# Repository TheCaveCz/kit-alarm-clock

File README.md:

# Alarm clock / Budík

## Česky

Stavebnice digitálních hodin s budíkem ovládaných přes WiFI.

* [Návod na stavbu](doc/manual-cz.md) ([PDF](doc/manual-cz.pdf))
* [Nastavení budíku a aplikace](doc/blynk-cz.md)
* [Nahrání nového firmware](doc/firmware-cz.md)

## English

Coming soon...

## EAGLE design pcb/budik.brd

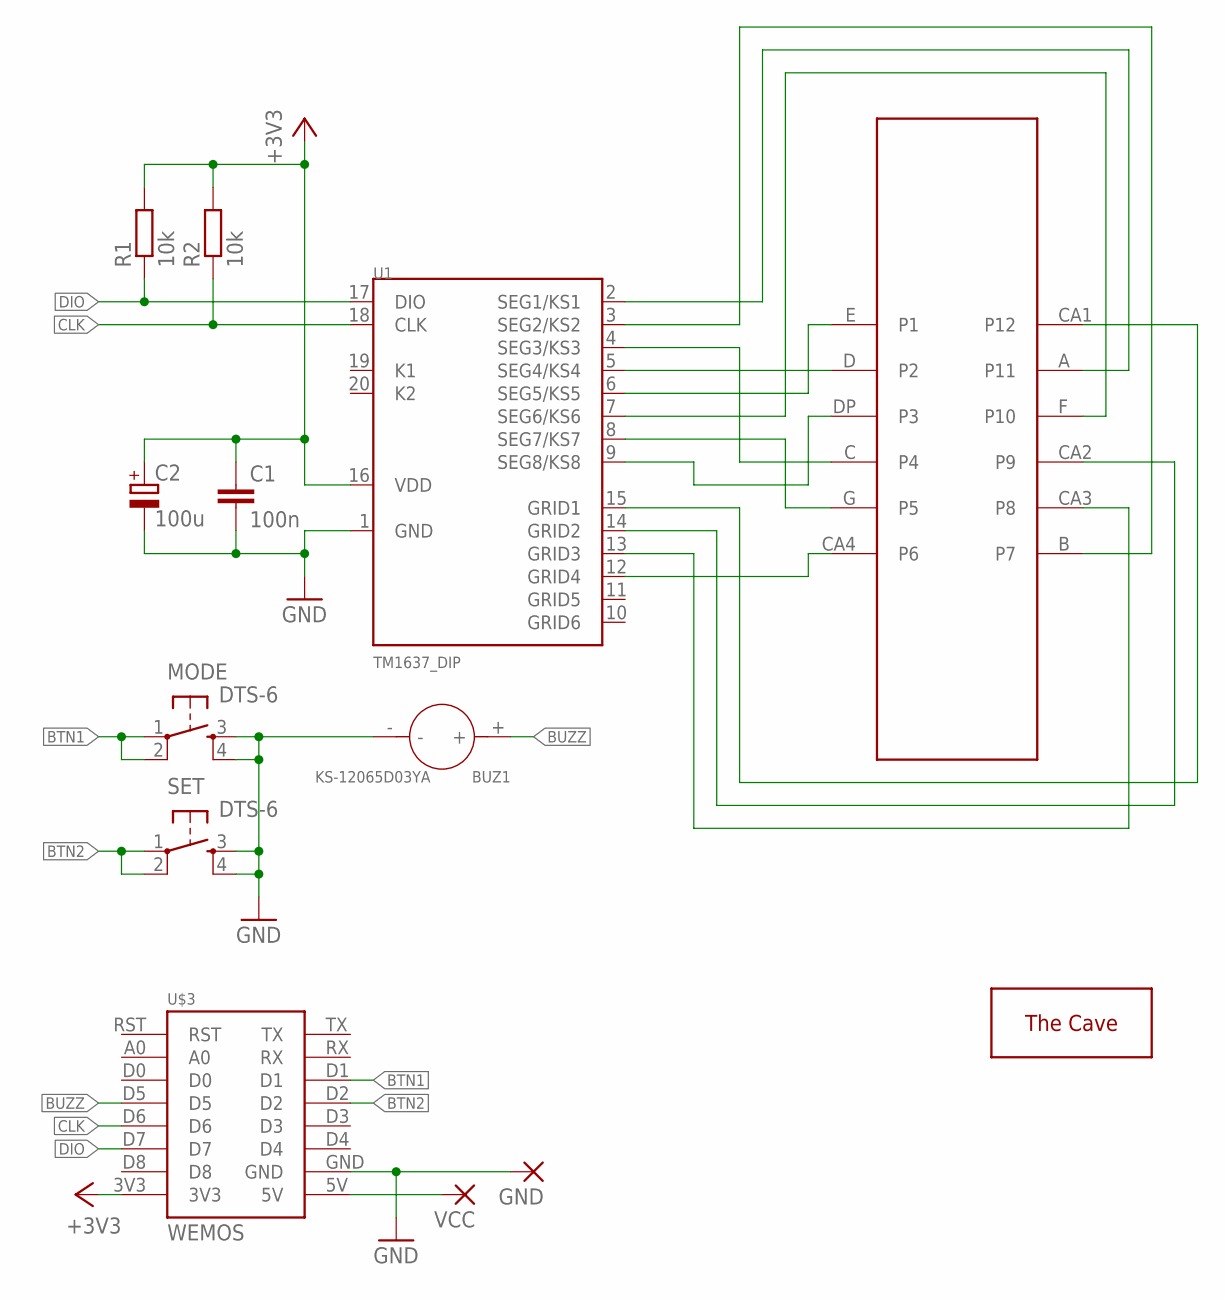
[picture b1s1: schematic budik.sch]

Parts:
BUZ1: KS-12065D03YA; BZ2-7.6-D12.0XH6.5MM
C1: 100n; C025-025X050
C2: 100u; E3,5-8
GND: WIREPADSMD1,27-254; SMD1,27-2,54
MODE: DTS-6
R1, R2: 10k; 0207/7
SET: DTS-6
U1: TM1637_DIP; DIL20
U$1: NFD-5642BX; DISPLAY
U$2: THECAVE_LOGO_NEW_TOP_SMALL; NEW_LOGO_SMALL_TOP
U$3: WEMOS
VCC: WIREPADSMD1,27-254; SMD1,27-2,54

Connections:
+3V3: C1.1, C2.+, R1.2, R2.2, U1.16 (VDD), U$3.3V3
BTN1: MODE.1, MODE.2, U$3.D1
BTN2: SET.1, SET.2, U$3.D2
BUZZ: BUZ1.+, U$3.D5
CLK: R2.1, U1.18 (CLK), U$3.D6
DIO: R1.1, U1.17 (DIO), U$3.D7
GND: BUZ1.-, C1.2, C2.-, GND.1, MODE.3, MODE.4, SET.3, SET.4, U1.1 (GND), U$3.GND
unnamed: U$3.5V, VCC.1
unnamed: U1.2 (SEG1/KS1), U$1.A (P11)
unnamed: U1.3 (SEG2/KS2), U$1.B (P7)
unnamed: U1.4 (SEG3/KS3), U$1.C (P4)
unnamed: U1.5 (SEG4/KS4), U$1.D (P2)
unnamed: U1.6 (SEG5/KS5), U$1.E (P1)
unnamed: U1.7 (SEG6/KS6), U$1.F (P10)
unnamed: U1.8 (SEG7/KS7), U$1.G (P5)
unnamed: U1.9 (SEG8/KS8), U$1.DP (P3)
unnamed: U1.15 (GRID1), U$1.CA1 (P12)
unnamed: U1.14 (GRID2), U$1.CA2 (P9)
unnamed: U1.13 (GRID3), U$1.CA3 (P8)
unnamed: U1.12 (GRID4), U$1.CA4 (P6)

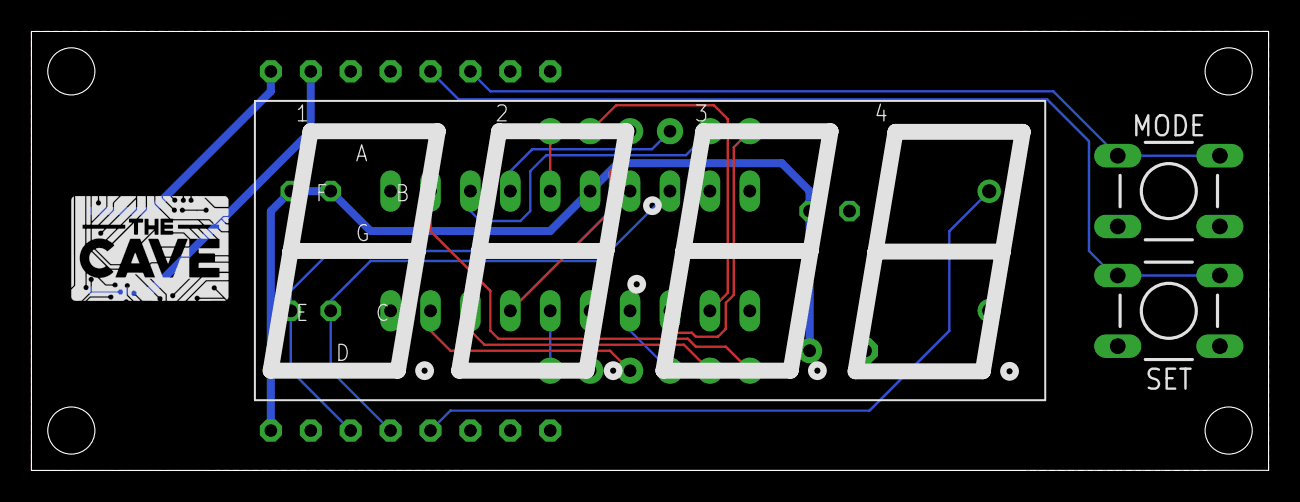
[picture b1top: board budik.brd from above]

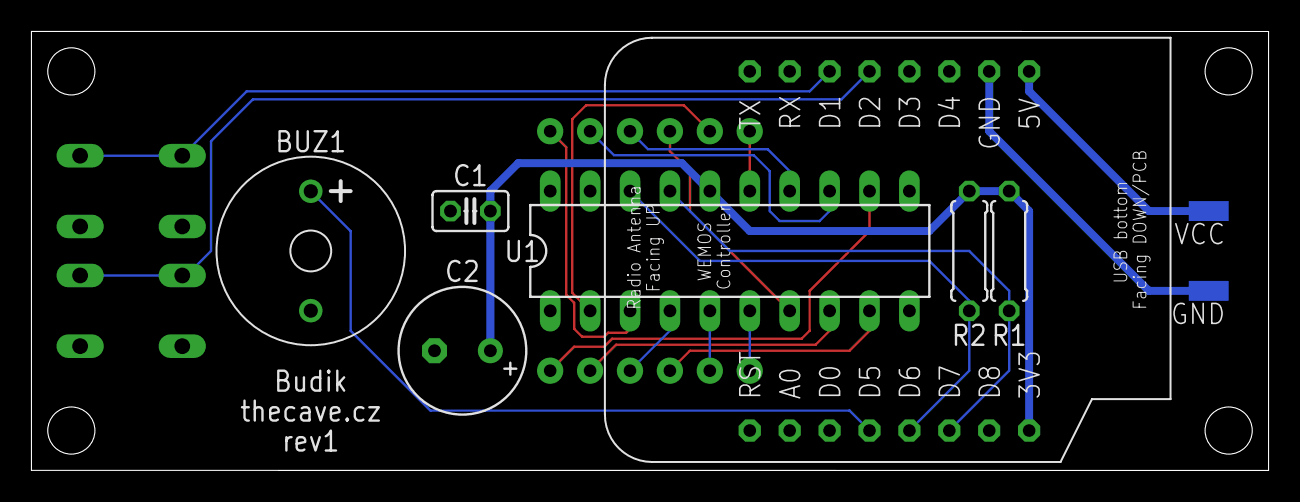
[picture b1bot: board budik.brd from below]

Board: 2 copper layers, 78.7 x 27.9 mm, 13 parts (9 on the bottom side), 20 nets.

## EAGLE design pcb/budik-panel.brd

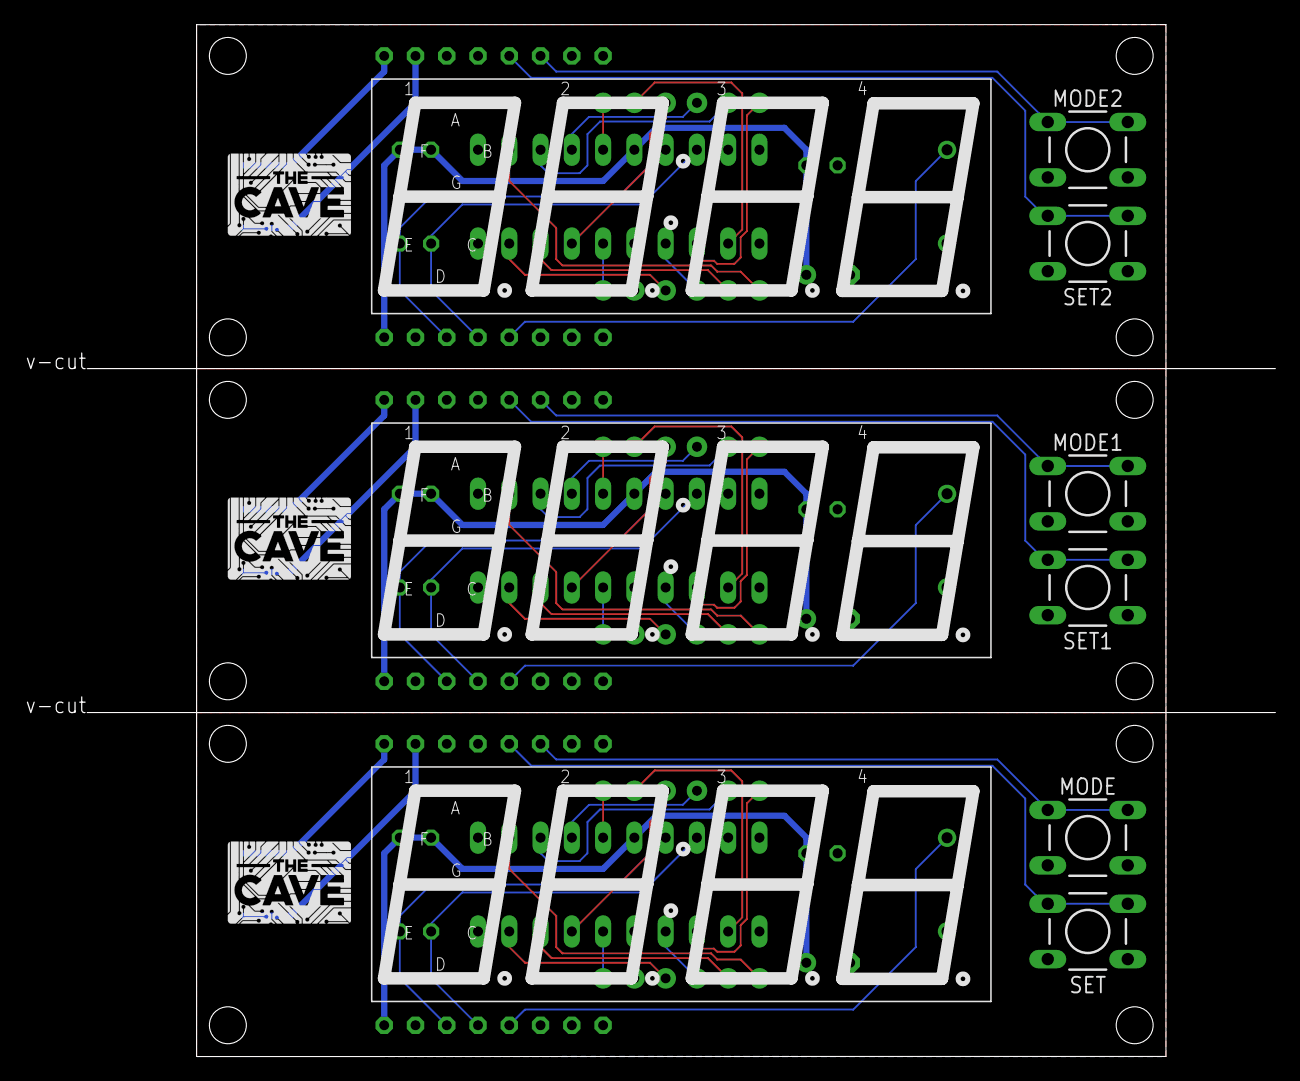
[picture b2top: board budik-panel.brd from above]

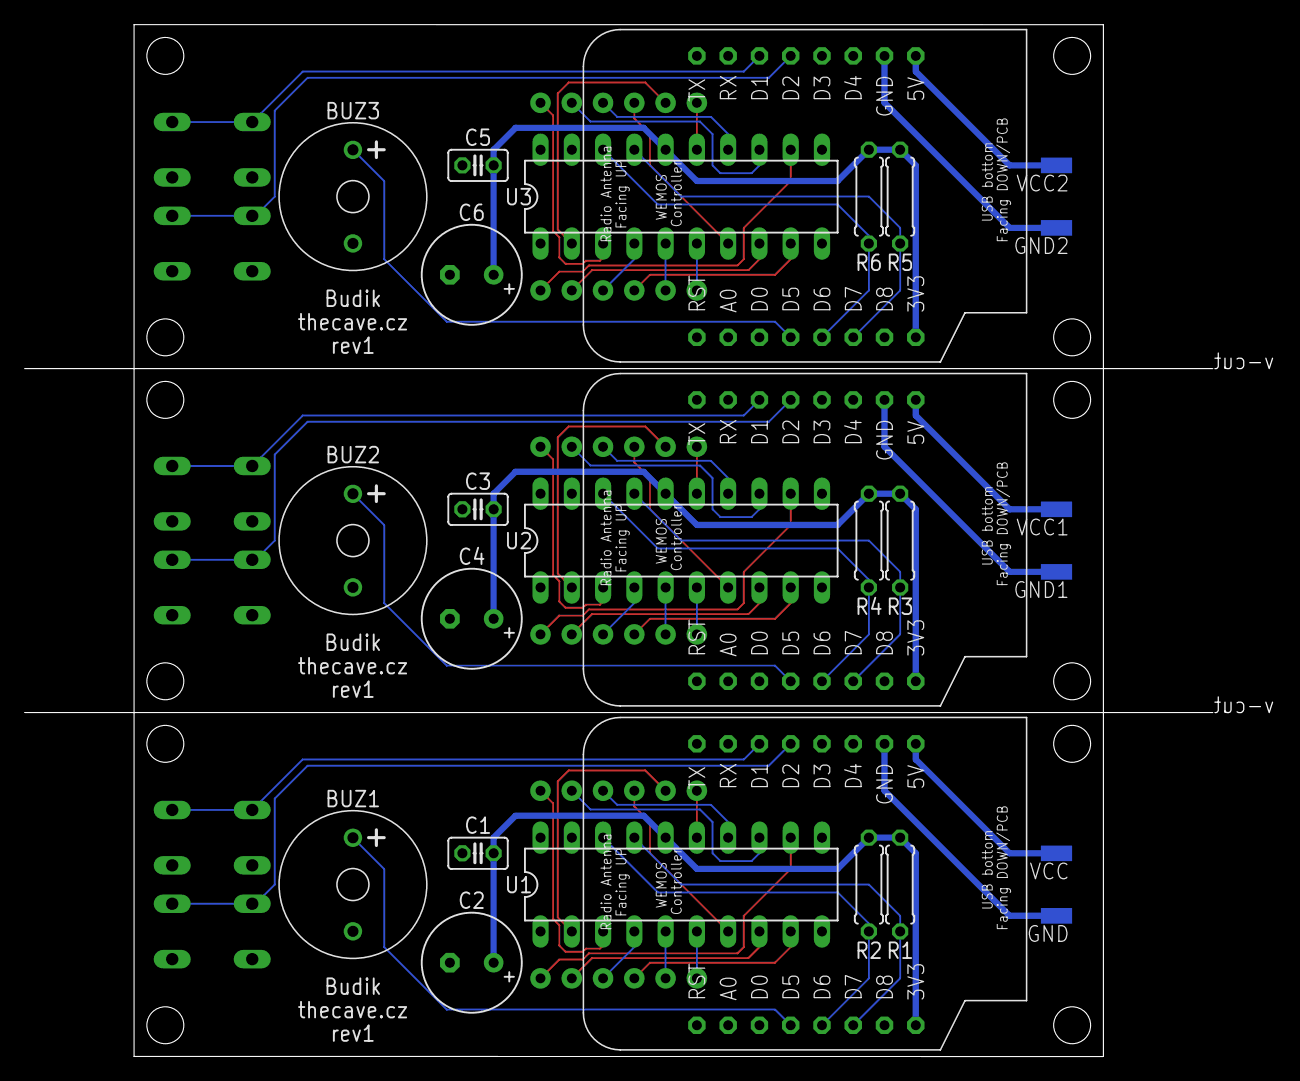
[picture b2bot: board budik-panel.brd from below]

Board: 2 copper layers, 101.6 x 83.8 mm, 39 parts (27 on the bottom side), 60 nets.

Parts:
BUZ1, BUZ2, BUZ3: KS-12065D03YA; BZ2-7.6-D12.0XH6.5MM
C1, C3, C5: 100n; C025-025X050
C2, C4, C6: 100u; E3,5-8
GND, GND1, GND2: SMD1,27-2,54
MODE, MODE1, MODE2: DTS-6
R1, R2, R3, R4, R5, R6: 10k; 0207/7
SET, SET1, SET2: DTS-6
U1, U2, U3: TM1637_DIP; DIL20
U$1, U$4, U$7: NFD-5642BX; DISPLAY
U$2, U$5, U$8: THECAVE_LOGO_NEW_TOP_SMALL; NEW_LOGO_SMALL_TOP
U$3, U$6, U$9: WEMOS
VCC, VCC1, VCC2: SMD1,27-2,54

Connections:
+3V1: C3.1, C4.+, R3.2, R4.2, U2.16, U$6.3V3
+3V2: C5.1, C6.+, R5.2, R6.2, U3.16, U$9.3V3
+3V3: C1.1, C2.+, R1.2, R2.2, U1.16, U$3.3V3
BTN1: MODE.1, MODE.2, U$3.D1
BTN2: SET.1, SET.2, U$3.D2
BTN3: MODE1.1, MODE1.2, U$6.D1
BTN4: SET1.1, SET1.2, U$6.D2
BTN5: MODE2.1, MODE2.2, U$9.D1
BTN6: SET2.1, SET2.2, U$9.D2
BUZZ: BUZ1.+, U$3.D5
BUZZ1: BUZ2.+, U$6.D5
BUZZ2: BUZ3.+, U$9.D5
CLK: R2.1, U1.18, U$3.D6
CLK1: R4.1, U2.18, U$6.D6
CLK2: R6.1, U3.18, U$9.D6
DIO: R1.1, U1.17, U$3.D7
DIO1: R3.1, U2.17, U$6.D7
DIO2: R5.1, U3.17, U$9.D7
GND: BUZ1.-, C1.2, C2.-, GND.1, MODE.3, MODE.4, SET.3, SET.4, U1.1, U$3.GND
GND1: BUZ2.-, C3.2, C4.-, GND1.1, MODE1.3, MODE1.4, SET1.3, SET1.4, U2.1, U$6.GND
GND2: BUZ3.-, C5.2, C6.-, GND2.1, MODE2.3, MODE2.4, SET2.3, SET2.4, U3.1, U$9.GND
unnamed: U$3.5V, VCC.1
unnamed: U1.2, U$1.A
unnamed: U1.3, U$1.B
unnamed: U1.4, U$1.C
unnamed: U1.5, U$1.D
unnamed: U1.6, U$1.E
unnamed: U1.7, U$1.F
unnamed: U1.8, U$1.G
unnamed: U1.9, U$1.DP
unnamed: U1.15, U$1.CA1
unnamed: U1.14, U$1.CA2
unnamed: U1.13, U$1.CA3
unnamed: U1.12, U$1.CA4
unnamed: U2.2, U$4.A
unnamed: U2.3, U$4.B
unnamed: U2.4, U$4.C
unnamed: U2.5, U$4.D
unnamed: U2.6, U$4.E
unnamed: U2.7, U$4.F
unnamed: U2.8, U$4.G
unnamed: U2.9, U$4.DP
unnamed: U2.15, U$4.CA1
unnamed: U2.14, U$4.CA2
unnamed: U2.13, U$4.CA3
unnamed: U2.12, U$4.CA4
unnamed: U$6.5V, VCC1.1
unnamed: U3.2, U$7.A
unnamed: U3.3, U$7.B
unnamed: U3.4, U$7.C
unnamed: U3.5, U$7.D
unnamed: U3.6, U$7.E
unnamed: U3.7, U$7.F
unnamed: U3.8, U$7.G
unnamed: U3.9, U$7.DP
unnamed: U3.15, U$7.CA1
unnamed: U3.14, U$7.CA2
unnamed: U3.13, U$7.CA3
unnamed: U3.12, U$7.CA4
unnamed: U$9.5V, VCC2.1

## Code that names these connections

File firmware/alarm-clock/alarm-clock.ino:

/*
 * Alarm clock kit firmware for Blynk app
 * 
 * The Cave, 2019
 * https://thecave.cz
 * 
 * Licensed under MIT License (see LICENSE file for details)
 * 
 * board: LOLIN(WEMOS) D1 R2 & mini
 * 
 */
#define BLYNK_PRINT Serial
#define BLYNK_NO_FANCY_LOGO

#include <ESP8266WiFi.h>
#include <ArduinoOTA.h>
#include <Ticker.h>
#include <EEPROM.h>
#include <WiFiUdp.h>

// https://github.com/blynkkk/blynk-library
#include <BlynkSimpleEsp8266.h>
#include <WidgetRTC.h>

// https://github.com/tzapu/WiFiManager
#include <WiFiManager.h>

// https://github.com/mathertel/OneButton
#include <OneButton.h>

// https://github.com/arkhipenko/TaskScheduler
#include <TaskScheduler.h>

// https://github.com/avishorp/TM1637
#include <TM1637Display.h>

// https://github.com/PaulStoffregen/Time
#include <TimeLib.h>


#define PIN_BUZZ D5
#define PIN_CLK D6
#define PIN_DATA D7
#define PIN_BTN1 D1
#define PIN_BTN2 D2

#define BLYNK_PIN_TIMEINPUT V0
#define BLYNK_PIN_ALARMENABLE V1
#define BLYNK_PIN_COUNTDOWN_MIN V2
#define BLYNK_PIN_COUNTDOWN_SEC V3
#define BLYNK_PIN_COUNTDOWN_START V4


// Logging over Serial
#define LOG_ENABLED 1

#define RECONNECT_INTERVAL 30000UL

#define WIFI_AP_NAME "alarm-clock-"

String chipId = String(ESP.getChipId(), HEX);
Scheduler scheduler;

void placeholder() {} // keep this function here

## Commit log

2019-05-09 Add firmware, 3d prints and pcb
2019-05-14 Add gerber files
2019-06-20 Add manual
2019-06-27 Add main firmware
2019-06-27 Add compiled firmware
2019-12-20 Adding blynk manual
